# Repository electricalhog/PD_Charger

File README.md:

## Description
This prototype board is being used as a hardware test platform for the fully integrated project of the USB-C PD Charger. The PCB is designed to include all possible inputs/outputs and allow for troubleshooting, while interfacing with an off-the-shelf microcontroller board (NUCLEO-G431RB). Using discrete components that mirror the ideal setup will allow for full functionality and flexibilty in development.
## Testing
So far the board has been proven to work with ST's UCPDMon software as a Power Delivery Source and also control the 4-switch buck-boost controller.

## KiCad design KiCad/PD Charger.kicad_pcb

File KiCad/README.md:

# PD_Charger

*Schematic*

*Board rendering*

[Digi-Key Cart](https://www.digikey.com/en/mylists/list/EXQTTTFIJZ)

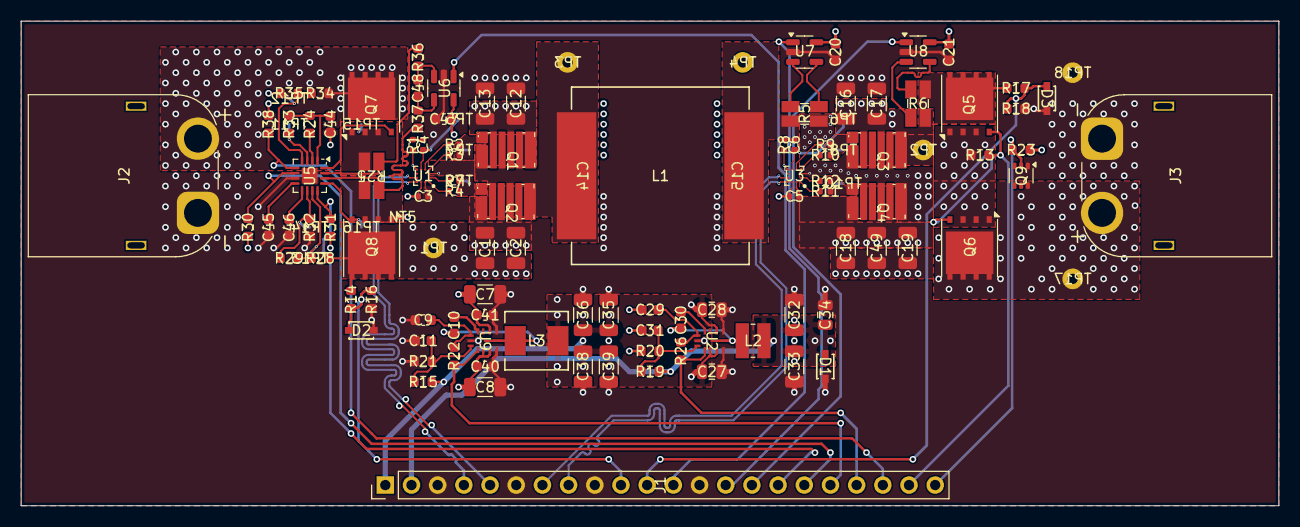
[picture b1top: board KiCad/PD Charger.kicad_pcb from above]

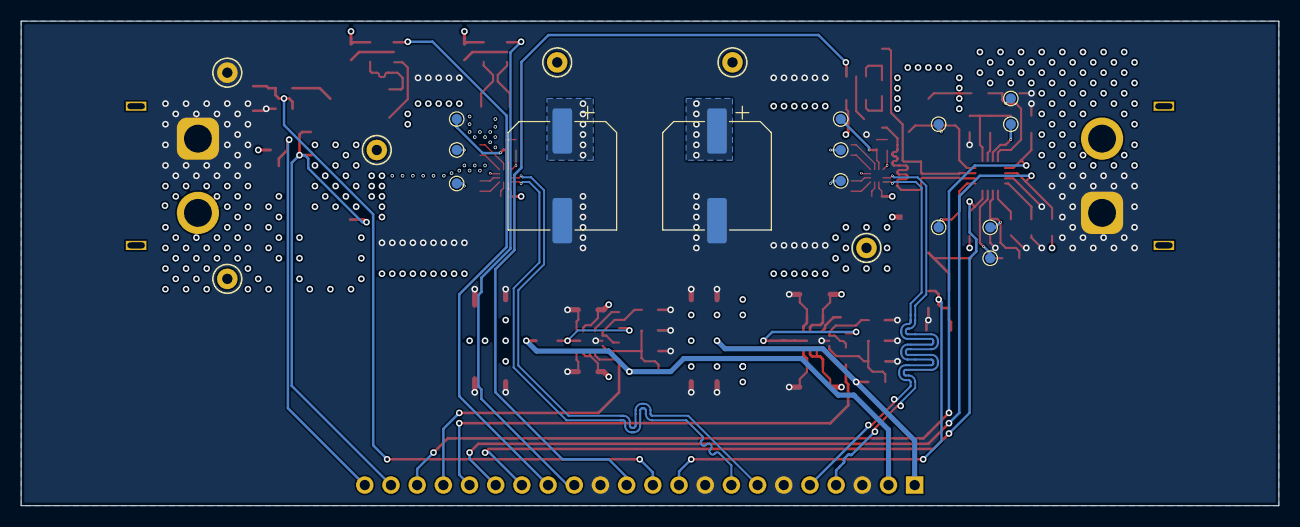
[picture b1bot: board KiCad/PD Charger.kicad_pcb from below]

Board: 4 copper layers, 122.0 x 47.0 mm, 123 parts (20 on the bottom side), 73 nets.

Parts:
C1, C2, C7, C8, C12, C13, C16, C17, C18, C19, C32, C33, C35, C36, C38, C39, C49: 10u; C_1206_3216Metric
C3, C5: 1u; C_0402_1005Metric
C4, C6: 100n; C_0402_1005Metric
C9, C29, C40, C41: 1u; C_0603_1608Metric
C10, C30: 100n; C_0603_1608Metric
C11, C31: 20p; C_0603_1608Metric
C14, C15: 82u; CP_Elec_10x7.9
C20, C21, C44, C47: 1uF; C_0603_1608Metric
C27, C28, C34: 0.47u; C_0805_2012Metric
C45: 20nF; C_0603_1608Metric
C46: 50nF; C_0603_1608Metric
C48: 1n; C_0603_1608Metric
D1, D2, D3: 3.425; CR_PLZ5V1C_VIS
J1: Conn_01x22; PinHeader_1x22_P2.54mm_Vertical
J2, J3: XT60_M; AMASS_XT60PW-M_1x02_P7.20mm_Horizontal
L1: 4.7u; L_Vishay_IHLP-6767
L2: 33u; L_Wuerth_MAPI-3015
L3: 10u; IND_PCC-M0530M-LP_PAN
NT5: NetTie_2; NetTie-2_SMD_Pad0.5mm
Q1, Q2, Q3, Q4: EPC2302; D0606F_100V
Q5, Q6, Q7, Q8: SiR5607DP; AO_DFN-8-1EP_5.55x5.2mm_P1.27mm_EP4.12x4.6mm
Q9: Q_Dual_NMOS_S1G1D2S2G2D1; SOT-363_SC-70-6
R1, R8: 0; R_0402_1005Metric
R2, R4, R9, R11: 2.2; R_0402_1005Metric
R3, R7, R10, R12: 1; R_0402_1005Metric
R5: 5m; R_Shunt_Ohmite_LVK12
R6: 12m; R_Shunt_Ohmite_LVK12
R13: 51k; R_0603_1608Metric
R14, R15, R17, R19, R22, R23, R26, R28, R30, R31, R38: 100k; R_0603_1608Metric
R16, R18: 5820; R_0603_1608Metric
R20: 43.2k; R_0603_1608Metric
R21: 24.9k; R_0603_1608Metric
R24, R33: 0; R_0603_1608Metric
R25: 2m; R_Shunt_Ohmite_LVK12
R29: 4.3k; R_0603_1608Metric
R32: 29k; R_0603_1608Metric
R34: 68k; R_0603_1608Metric
R35: 1.2k; R_0603_1608Metric
R36, R37: 10; R_0603_1608Metric
TP1, TP2, TP3, TP4, TP17, TP18: TestPoint; TestPoint_Keystone_5000-5004_Miniature
TP5, TP6, TP7, TP8, TP9, TP10, TP11, TP12, TP13, TP14, TP15, TP16: TestPoint; TestPoint_Pad_D1.0mm
U1, U3: WLCSP1.6x1.6-12B
U2: LMR36006BRNXT; RNX0012B
U5: ADM1270ACPZ; LFCSP-16-1EP_3x3mm_P0.5mm_EP1.5x1.5mm
U6: INA293A2; SOT-23-5
U7, U8: INA281A2; SOT-23-5
U9: LMR36015BRNXT; RNX0012B

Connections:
+3V3: C20.1, C21.1, C32.1, C33.1, C34.2, C47.1, D1.1 (K), J1.2, L2.2, R19.1, R23.2, R30.2, R31.2, U6.5 (V+), U7.5 (V+), U8.5 (V+)
+5V: C3.1, C5.1, C27.2, C28.2, C35.1, C36.1, C38.1, C39.1, J1.1, L3.2, R15.1, U1.A3 (VCC), U2.2 (VIN), U2.9 (EN), U2.10 (VIN), U3.A3 (VCC)
/3V3_GOOD: J1.19, R26.1, U2.8 (PG)
/3v3 Regulator/BST: C30.1, U2.4 (BST)
/3v3 Regulator/FB: C31.1, R19.2, R20.1, U2.7 (FB)
/3v3 Regulator/VCC: C29.1, R26.2, U2.5 (VCC)
/5V_GOOD: J1.18, R22.1, U9.8 (PG)
/5v Regulator/BST: C10.1, U9.4 (BST)
/5v Regulator/FB: C11.1, R15.2, R21.1, U9.7 (FB)
/5v Regulator/VCC: C9.1, R22.2, U9.5 (VCC)
/DC-DC/G1: Q1.1 (G), R2.2, R3.2, TP7.1
/DC-DC/G2: Q2.1 (G), R4.2, R7.2, TP9.1
/DC-DC/G3: Q3.1 (G), R9.2, R10.2, TP8.1
/DC-DC/G4: Q4.1 (G), R11.2, R12.2, TP10.1
/DC-DC/IDN: R6.3, U8.4 (Vin-)
/DC-DC/IDP: R6.2, U8.3 (Vin+)
/DC-DC/LSN: R5.3, U7.4 (Vin-)
/DC-DC/LSP: R5.2, U7.3 (Vin+)
/DC-DC/SW1: L1.1, Q1.2 (S), Q1.4 (S), Q1.6 (S), Q2.3 (D), Q2.5 (D), Q2.7 (D), R1.2, TP3.1, U1.C1 (PHASE), U1.D4 (PHASE)
/DC-DC/SW2: Q3.2 (S), Q3.4 (S), Q3.6 (S), Q4.3 (D), Q4.5 (D), Q4.7 (D), R5.4, R8.2, U3.C1 (PHASE), U3.D4 (PHASE)
/DC-DC/SW2a: L1.2, R5.1
/DC-DC/VOUTa: C15.1, C16.1, C17.1, C18.1, C19.1, C49.1, Q3.3 (D), Q3.5 (D), Q3.7 (D), R6.1, TP2.1
/ID_MON: J1.15, U8.1 (OUT)
/IL_MON: J1.14, U7.1 (OUT)
/INPUT_EN: J1.20, R38.2, U5.5 (ENABLE)
/IS_GOOD: J1.17, R30.1, U5.6 (~FAULT)
/IS_MON: J1.12, U6.1 (OUT)
/Input Protection/FB_PG: R29.1, R32.2, TP14.1, U5.10 (FB_PG)
/Input Protection/FLB: R28.1, R29.2, TP13.1, U5.11 (FLB)
/Input Protection/G_BP: Q8.4 (G), TP16.1, U5.13 (GATE)
/Input Protection/G_RP: Q7.4 (G), TP15.1, U5.16 (RPFG)
/Input Protection/ISET: R24.2, U5.2 (ISET)
/Input Protection/OV: R34.1, R35.2, TP12.1, U5.4 (OV)
/Input Protection/Q7_S: Q7.1 (S), Q7.2 (S), Q7.3 (S), R25.1
/Input Protection/Q8_S: NT5.2, Q8.1 (S), Q8.2 (S), Q8.3 (S), R25.4
/Input Protection/SENSE+: R25.2, R36.2, U5.15 (VCC)
/Input Protection/SENSE-: R25.3, R37.2, U5.14 (SENSE-)
/Input Protection/SENSE_FILTERED+: C48.2, R36.1, U6.3 (Vin+)
/Input Protection/SENSE_FILTERED-: C48.1, R37.1, U6.4 (Vin-)
/Input Protection/TIMER: C45.1, U5.8 (TIMER)
/Input Protection/TIMER_OFF: C46.1, U5.9 (TIMER_OFF)
/Input Protection/UV: R33.1, TP11.1, U5.3 (UV)
/Input Protection/VCAP: C44.1, R24.1, R33.2, U5.1 (VCAP)
/OUTPUT_DIS: J1.22, Q9.2 (G), R23.1
/OUTPUT_EN: J1.21, Q5.4 (G), Q6.4 (G), R13.2
/Output Switch/COM_S: Q5.1 (S), Q5.2 (S), Q5.3 (S), Q6.1 (S), Q6.2 (S), Q6.3 (S), R13.1
/PHASE_1_N: J1.5, U1.A4 (LI)
/PHASE_1_P: J1.4, U1.B4 (HI)
/PHASE_2_N: J1.8, U3.A4 (LI)
/PHASE_2_P: J1.7, U3.B4 (HI)
/VD_MON: D3.1 (K), J1.11, R17.2, R18.1
/VS_GOOD: J1.16, R31.1, U5.12 (PWRGD)
/VS_MON: D2.1 (K), J1.10, R14.2, R16.1
GND: C1.2, C2.2, C3.2, C5.2, C7.2, C8.2, C9.2, C11.2, C12.2, C13.2, C14.2, C15.2, C16.2, C17.2, C18.2, C19.2, C20.2, C21.2, C27.1, C28.1, C29.2, C31.2, C32.2, C33.2, C34.1, C35.2, C36.2, C38.2, C39.2, C40.2, C41.2, C44.2, C45.2, C46.2, C47.2, C49.2, D1.2 (A), D2.2 (A), D3.2 (A), J1.3, J1.6, J1.9, J1.13, J2.1, J3.1, Q2.2 (S), Q2.4 (S), Q2.6 (S), Q4.2 (S), Q4.4 (S), Q4.6 (S), Q9.1 (S), R16.2, R18.2, R20.2, R21.2, R32.1, R35.1, R38.1, TP18.1, U1.A2 (GND), U2.1 (PGND), U2.6 (AGND), U2.11 (PGND), U3.A2 (GND), U5.7 (GND), U5.17 (EP), U6.2 (GND), U7.2 (GND), U8.2 (GND), U9.1 (PGND), U9.6 (AGND), U9.11 (PGND)
unnamed: C4.2, R1.1
unnamed: C6.2, R8.1
unnamed: C4.1, TP5.1, U1.D3 (BOOT)
unnamed: R7.1, U1.B1 (LGH)
unnamed: R4.1, U1.A1 (LGL)
unnamed: R2.1, U1.D2 (UGH)
unnamed: R3.1, U1.D1 (UGL)
unnamed: C30.2, L2.1, U2.12 (SW)
unnamed: C6.1, TP6.1, U3.D3 (BOOT)
unnamed: R12.1, U3.B1 (LGH)
unnamed: R11.1, U3.A1 (LGL)
unnamed: R9.1, U3.D2 (UGH)
unnamed: R10.1, U3.D1 (UGL)
unnamed: C10.2, L3.1, U9.12 (SW)
VBUS: J3.2, Q6.5 (D), Q9.6 (D), TP17.1
VCC: C7.1, C8.1, C40.1, C41.1, NT5.1, U9.2 (VIN), U9.9 (EN), U9.10 (VIN)
VD: Q5.5 (D), R6.4, R17.1
VIN: J2.2, Q7.5 (D), R34.2
VS: C1.1, C2.1, C12.1, C13.1, C14.1, Q1.3 (D), Q1.5 (D), Q1.7 (D), Q8.5 (D), R14.1, R28.2, TP1.1

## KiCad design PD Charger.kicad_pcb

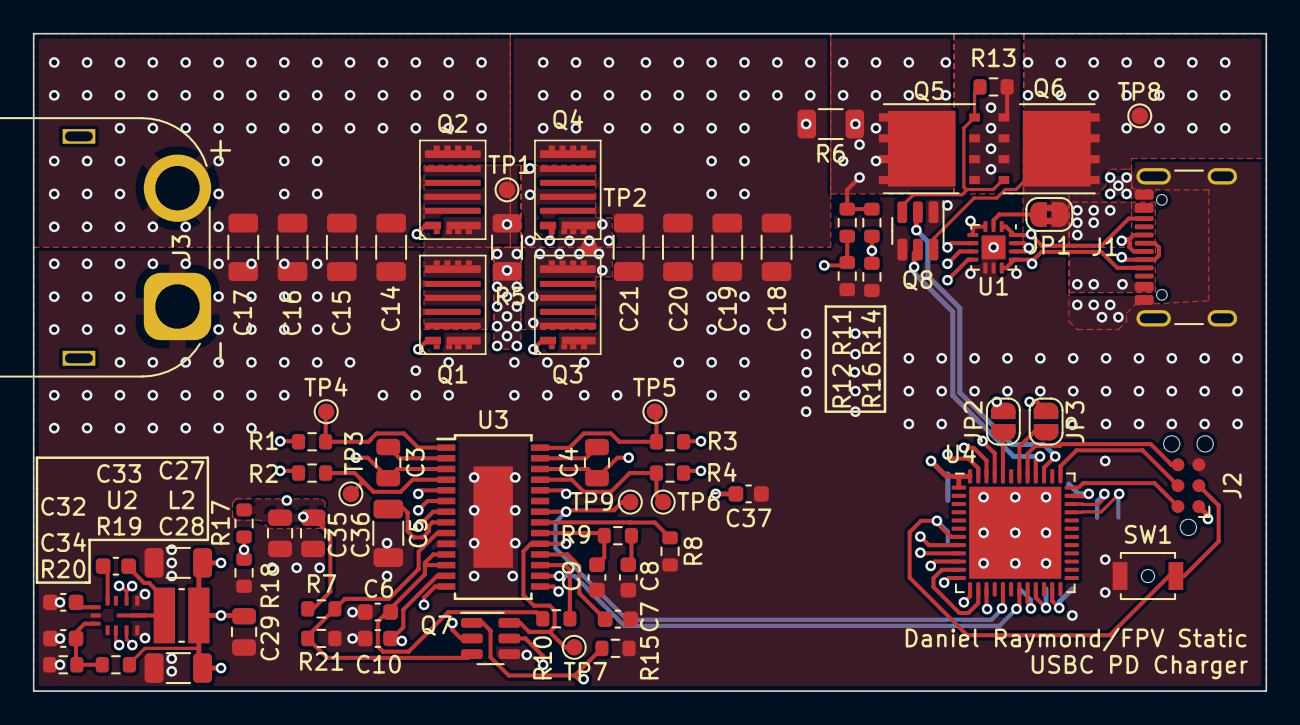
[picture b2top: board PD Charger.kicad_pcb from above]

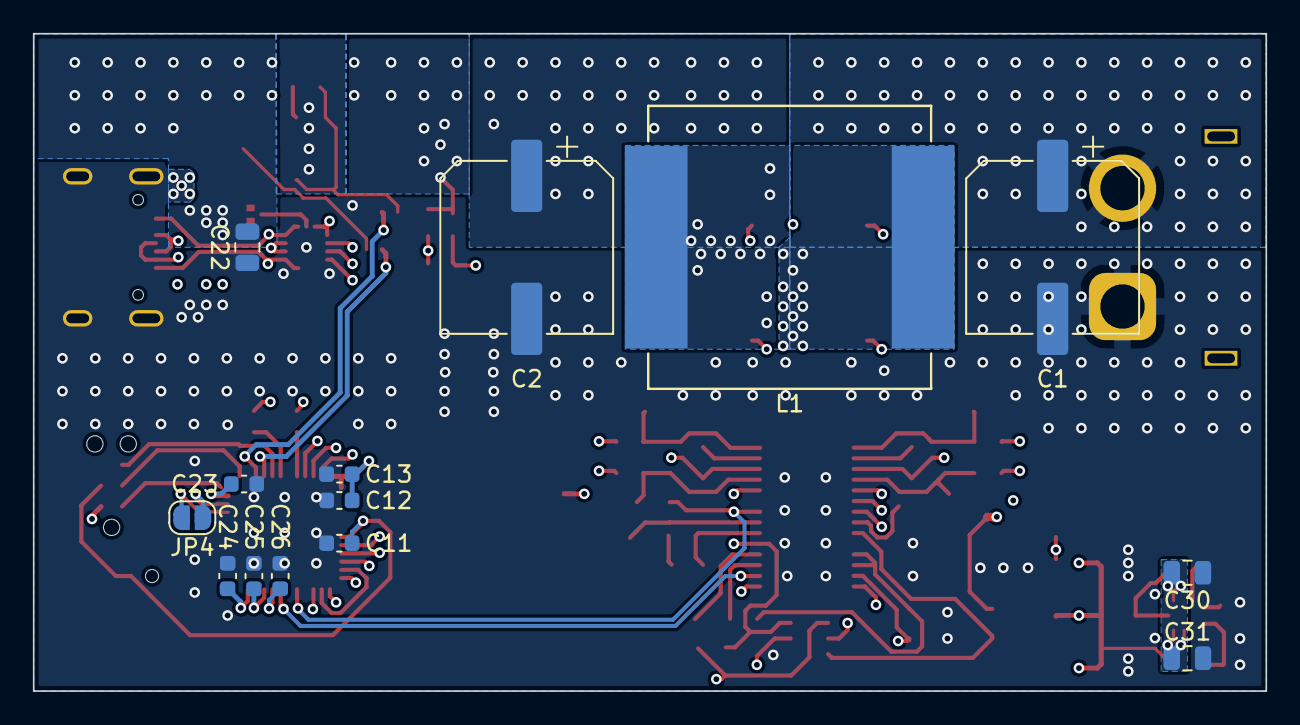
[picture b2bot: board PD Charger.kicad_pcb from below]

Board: 4 copper layers, 75.0 x 40.0 mm, 89 parts (14 on the bottom side), 60 nets.

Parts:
C1, C2: 82u; CP_Elec_10x7.9
C3, C4, C22, C29, C30, C31, C35, C36: 0.47u; C_0805_2012Metric
C5, C14, C15, C16, C17, C18, C19, C20, C21, C27, C28: 10u; C_1206_3216Metric
C6, C25: 0.47u; C_0603_1608Metric
C7, C12, C13, C23, C24: 0.1u; C_0603_1608Metric
C8: 4.7n; C_0603_1608Metric
C9: 100p; C_0603_1608Metric
C10: 4.7u; C_0603_1608Metric
C11, C26, C33: 100n; C_0603_1608Metric
C32, C37: 1u; C_0603_1608Metric
C34: 20p; C_0603_1608Metric
J1: USB_C_Receptacle_USB2.0; USB_C_Receptacle_GCT_USB4105-xx-A_16P_TopMnt_Horizontal
J2: Conn_ARM_SWD_TagConnect_TC2030; Tag-Connect_TC2030-IDC-NL_2x03_P1.27mm_Vertical
J3: XT60_M; AMASS_XT60PW-M_1x02_P7.20mm_Horizontal
JP1: SolderJumper_2_Bridged; SolderJumper-2_P1.3mm_Bridged2Bar_RoundedPad1.0x1.5mm
JP2, JP3, JP4: SolderJumper_2_Open; SolderJumper-2_P1.3mm_Open_RoundedPad1.0x1.5mm
L1: 4.7u; L_Vishay_IHLP-6767
L2: 33u; L_Wuerth_MAPI-3015
Q1, Q2, Q3, Q4: NMOS; ECP2302
Q5, Q6: NTMFS002P03; AO_DFN-8-1EP_5.55x5.2mm_P1.27mm_EP4.12x4.6mm
Q7, Q8: Q_Dual_NMOS_S1G1D2S2G2D1; SOT-23-6
R1, R2, R3, R4: 1; R_0603_1608Metric
R5: 5m; R_1206_3216Metric
R6: 20m; R_1206_3216Metric
R7, R10, R14, R17, R19: 100k; R_0603_1608Metric
R8, R13: 51k; R_0603_1608Metric
R9: 27k; R_0603_1608Metric
R11: 36k; R_0603_1608Metric
R12: 9k; R_0603_1608Metric
R15: 752; R_0603_1608Metric
R16, R18: 5820; R_0603_1608Metric
R20: 43.2k; R_0603_1608Metric
R21: 33k; R_0603_1608Metric
SW1: SW_MEC_5G; SW_SPST_B3U-1000P-B
TP1, TP2, TP3, TP4, TP5, TP6, TP7, TP8, TP9: TestPoint_Small; TestPoint_Pad_D1.0mm
U1: FUSB302B01MPX; WQFN-14-1EP_2.5x2.5mm_P0.5mm_EP1.45x1.45mm
U2: LMR36006BRNXT; RNX0012B
U3: LT8390xFE; TSSOP-28-1EP_4.4x9.7mm_P0.65mm
U4: STM32G431C6Ux; QFN-48-1EP_7x7mm_P0.5mm_EP5.6x5.6mm

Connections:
+3V3: C12.1, C13.1, C23.1, C24.1, C25.1, C27.1, C28.1, C29.2, J2.1 (VCC), L2.2, R19.1, U1.3 (VDD), U1.4 (VDD), U1.12 (VCONN), U1.13 (VCONN), U4.1 (VBAT), U4.21 (VDDA), U4.23 (VDD), U4.35 (VDD), U4.48 (VDD)
/CC1: J1.A5 (CC1), JP2.1 (A), U1.10 (CC1), U1.11 (CC1)
/CC2: J1.B5 (CC2), JP3.1 (A), U1.1 (CC2), U1.14 (CC2)
/COM_S: Q5.1 (S), Q5.2 (S), Q5.3 (S), Q6.1 (S), Q6.2 (S), Q6.3 (S), R13.1
/EN: Q7.3 (D), R7.2, R21.2, U3.9 (EN/UVLO)
/FB: Q7.6 (D), R11.1, R12.2, TP7.1, U3.19 (FB)
/G1: Q1.2 (G), R1.2
/G2: Q2.2 (G), R2.2
/G3: Q3.2 (G), R3.2
/G4: Q4.2 (G), R4.2
/INT_N: U1.5 (INT_N), U4.47 (PB9)
/ISMON: U3.16 (ISMON), U4.19 (PB2)
/LOADEN: Q8.5 (G), U4.40 (PC11)
/OUTDIS: Q8.2 (G), U4.39 (PC10)
/RT: R8.1, U3.21 (RT)
/SCL: U1.6 (SCL), U4.46 (PB8)
/SDA: U1.7 (SDA), U4.45 (PB7)
/SS: C7.1, U3.18 (SS)
/SWCLK: J2.4 (SWCLK), U4.37 (PA14)
/SWDIO: J2.2 (SWDIO), U4.36 (PA13)
/SWO: J2.6 (SWO), U4.41 (PB3)
/SYNC: TP9.1, U3.22 (SYNC/SPRD), U4.17 (PB0)
/USB_DN: J1.A7 (D-), J1.B7 (D-), JP4.2 (B), U4.33 (PA11)
/USB_DP: J1.A6 (D+), J1.B6 (D+), JP4.1 (A), U4.34 (PA12)
/VADJ: Q7.1 (S), R15.1, U4.15 (PA7)
/VADJ_AMP: U4.11 (PA3), U4.14 (PA6)
/VBUS: C22.2, J1.A4 (VBUS), J1.A9 (VBUS), J1.B4 (VBUS), J1.B9 (VBUS), JP1.2 (B), Q6.5 (D), Q8.6 (D), TP8.1
/VC: C9.1, R9.1, U3.20 (VC)
/VCTRLI: C10.1, U3.13 (CTRL1), U4.12 (PA4)
/VCTRLV: Q7.2 (G), U4.10 (PA2)
/VIN_SENSE: R17.2, R18.1, U4.8 (PA0)
/VOUT_SENSE: R14.2, R16.1, U4.9 (PA1)
/VREF: C6.1, R10.1, U3.11 (LOADEN), U3.12 (VREF)
/VREF+: C26.1, U4.20 (VREF+)
/~PGOOD: R10.2, U3.17 (~PGOOD)
/~RST: C11.1, J2.3 (~RESET), SW1.2, U4.7 (PG10)
/~RUN: Q7.5 (G), U4.13 (PA5)
GND: C1.2, C2.2, C5.2, C6.2, C7.2, C8.2, C9.2, C10.2, C11.2, C12.2, C13.2, C14.2, C15.2, C16.2, C17.2, C18.2, C19.2, C20.2, C21.2, C22.1, C23.2, C24.2, C25.2, C26.2, C27.2, C28.2, C29.1, C30.1, C31.1, C32.2, C34.2, C35.1, C36.1, C37.2, J1.A1 (GND), J1.A12 (GND), J1.B1 (GND), J1.B12 (GND), J1.S1 (SHIELD), J2.5 (GND), J3.1, Q1.3 (S), Q3.3 (S), Q7.4 (S), Q8.1 (S), Q8.4 (S), R8.2, R12.1, R15.2, R16.2, R18.2, R20.2, R21.1, SW1.1, U1.8 (GND), U1.9 (GND), U1.15 (GND), U2.1 (PGND), U2.6 (AGND), U2.11 (PGND), U3.10 (TEST), U3.29 (GND), U4.49 (VSS)
IS: C2.1, C18.1, C19.1, C20.1, C21.1, Q4.1 (D), R6.2, U3.14 (ISP)
LS: L1.1, R5.2, U3.6 (LSN)
unnamed: C8.1, R9.2
unnamed: JP1.1 (A), U1.2 (VBUS)
unnamed: JP2.2 (B), U4.44 (PB6)
unnamed: JP3.2 (B), U4.42 (PB4)
unnamed: Q5.4 (G), Q6.4 (G), Q8.3 (D), R13.2
unnamed: C33.1, U2.4 (BST)
unnamed: C34.1, R19.2, R20.1, U2.7 (FB)
unnamed: C33.2, L2.1, U2.12 (SW)
unnamed: C32.1, U2.5 (VCC)
unnamed: R1.1, TP4.1, U3.1 (BG1)
unnamed: R3.1, TP5.1, U3.28 (BG2)
unnamed: C3.1, U3.2 (BST1)
unnamed: C4.2, U3.27 (BST2)
unnamed: R2.1, TP3.1, U3.4 (TG1)
unnamed: R4.1, TP6.1, U3.25 (TG2)
SW1: C3.2, Q1.1 (D), Q2.3 (S), R5.1, TP1.1, U3.3 (SW1), U3.5 (LSP)
SW2: C4.1, L1.2, Q3.1 (D), Q4.3 (S), TP2.1, U3.26 (SW2)
VD: C37.1, Q5.5 (D), R6.1, R11.2, R14.1, U3.15 (ISN), U3.24 (VOUT)
VDD: C5.1, U3.8 (INTVCC)
VS: C1.1, C14.1, C15.1, C16.1, C17.1, C30.2, C31.2, C35.2, C36.2, J3.2, Q2.1 (D), R7.1, R17.1, U2.2 (VIN), U2.9 (EN), U2.10 (VIN), U3.7 (VIN)

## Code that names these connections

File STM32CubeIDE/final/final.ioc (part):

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Mcu.Name=STM32G474R(B-C-E)Tx
Mcu.Package=LQFP64
Mcu.UserName=STM32G474RETx
PA0.GPIOParameters=GPIO_Label
PA0.GPIO_Label=VS_MON
PA0.Mode=IN1-Single-Ended
PA0.Signal=ADC1_IN1
PA1.GPIOParameters=GPIO_Label
PA1.GPIO_Label=IL_MON
PA1.Signal=SharedAnalog_PA1
PA10.GPIOParameters=GPIO_Label
PA10.GPIO_Label=PHASE_2_P
PA10.Mode=Output_TB1TB2
PA10.Signal=HRTIM1_CHB1
PA11.GPIOParameters=GPIO_Label
PA11.GPIO_Label=PHASE_2_N
PA11.Mode=Output_TB1TB2
PA11.Signal=HRTIM1_CHB2
PA12.GPIOParameters=GPIO_PuPd,GPIO_Label
PA12.GPIO_Label=VS_GOOD
PA12.GPIO_PuPd=GPIO_PULLUP
PA12.Mode=Fault_Enable1
PA12.Signal=HRTIM1_FLT1
PA13.GPIOParameters=GPIO_Label
PA13.GPIO_Label=T_SWDIO
PA13.Mode=Serial_Wire
PA13.Signal=SYS_JTMS-SWDIO
PA14.GPIOParameters=GPIO_Label
PA14.GPIO_Label=T_SWCLK
PA14.Mode=Serial_Wire
PA14.Signal=SYS_JTCK-SWCLK
PA15.GPIOParameters=GPIO_PuPd,GPIO_Label
PA15.GPIO_Label=IS_GOOD
PA15.GPIO_PuPd=GPIO_PULLUP
PA15.Mode=Fault_Enable2
PA15.Signal=HRTIM1_FLT2
PA2.Mode=Asynchronous
PA2.Signal=LPUART1_TX
PA3.Mode=Asynchronous
PA3.Signal=LPUART1_RX
PA4.GPIOParameters=GPIO_Label
PA4.GPIO_Label=VS_MON
PA4.Mode=IN17-Single-Ended
PA4.Signal=ADC2_IN17
PA6.Mode=ExternalOutput
PA6.Signal=COMP1_OUT
PA8.GPIOParameters=GPIO_Label
PA8.GPIO_Label=PHASE_1_P
PA8.Mode=Output_TA1TA2
PA8.Signal=HRTIM1_CHA1
PA9.GPIOParameters=GPIO_Label
PA9.GPIO_Label=PHASE_1_N
PA9.Mode=Output_TA1TA2
PA9.Signal=HRTIM1_CHA2
PB0.GPIOParameters=GPIO_Label
PB0.GPIO_Label=IS_MON
PB0.Mode=IN15-Single-Ended
PB0.Signal=ADC1_IN15
PB3.GPIOParameters=GPIO_Label
PB3.GPIO_Label=T_SWO
PB3.Signal=SYS_JTDO-SWO
PB4.Mode=Source_AllSignals
PB4.Signal=UCPD1_CC2
PB6.Mode=Source_AllSignals
PB6.Signal=UCPD1_CC1
PB8-BOOT0.Mode=I2C
PB8-BOOT0.Signal=I2C1_SCL
PB9.Mode=I2C
PB9.Signal=I2C1_SDA
PC1.GPIOParameters=GPIO_Label
PC1.GPIO_Label=ID_MON
PC1.Mode=IN7-Single-Ended
PC1.Signal=ADC1_IN7
PC14-OSC32_IN.GPIOParameters=GPIO_Label
PC14-OSC32_IN.GPIO_Label=RCC_OSC32_IN
PC14-OSC32_IN.Mode=LSE-External-Oscillator
PC14-OSC32_IN.Signal=RCC_OSC32_IN
PC15-OSC32_OUT.GPIOParameters=GPIO_Label
PC15-OSC32_OUT.GPIO_Label=RCC_OSC32_OUT
PC15-OSC32_OUT.Mode=LSE-External-Oscillator
PC15-OSC32_OUT.Signal=RCC_OSC32_OUT
PC7.GPIOParameters=GPIO_Label
PC7.GPIO_Label=INPUT_EN
PC7.Signal=GPIO_Output
PC8.GPIOParameters=GPIO_Label
PC8.GPIO_Label=OUTPUT_EN
PC8.Signal=GPIO_Output
PC9.GPIOParameters=GPIO_Label
PC9.GPIO_Label=OUTPUT_DIS
PC9.Signal=GPIO_Output
PF0-OSC_IN.GPIOParameters=GPIO_Label
PF0-OSC_IN.GPIO_Label=RCC_OSC_IN
PF0-OSC_IN.Mode=HSE-External-Oscillator
PF0-OSC_IN.Signal=RCC_OSC_IN
PF1-OSC_OUT.GPIOParameters=GPIO_Label
PF1-OSC_OUT.GPIO_Label=RCC_OSC_OUT
PF1-OSC_OUT.Mode=HSE-External-Oscillator
PF1-OSC_OUT.Signal=RCC_OSC_OUT
RCC.HSE_VALUE=24000000
RCC.SYSCLKFreq_VALUE=170000000
RCC.SYSCLKSource=RCC_SYSCLKSOURCE_PLLCLK
board=NUCLEO-G474RE
boardIOC=true

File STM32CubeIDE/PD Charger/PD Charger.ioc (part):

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Mcu.Name=STM32G431C(6-8-B)Ux
Mcu.Package=UFQFPN48
Mcu.UserName=STM32G431C6Ux
PA0.Mode=INM
PA0.Signal=COMP1_INM
PA1.Mode=INP
PA1.Signal=COMP1_INP
PA10.GPIOParameters=GPIO_Label
PA10.GPIO_Label=INT_N
PA10.Signal=GPXTI10
PA13.Mode=Serial_Wire
PA13.Signal=SYS_JTMS-SWDIO
PA14.Mode=Serial_Wire
PA14.Signal=SYS_JTCK-SWCLK
PA2.Mode=Asynchronous
PA2.Signal=LPUART1_TX
PA3.Mode=Asynchronous
PA3.Signal=LPUART1_RX
PA4.GPIOParameters=GPIO_Label
PA4.GPIO_Label=VCTRL
PA4.Signal=COMP_DAC11_group
PA5.GPIOParameters=GPIO_Label
PA5.GPIO_Label=ICTRL
PA5.Signal=COMP_DAC12_group
PA6.GPIOParameters=GPIO_Label
PA6.GPIO_Label=VDMON
PA6.Mode=IN3-Single-Ended
PA6.Signal=ADC2_IN3
PA7.GPIOParameters=GPIO_Label
PA7.GPIO_Label=IDMON
PA7.Mode=IN4-Single-Ended
PA7.Signal=ADC2_IN4
PA8.Mode=I2C
PA8.Signal=I2C2_SDA
PA9.Mode=I2C
PA9.Signal=I2C2_SCL
PB0.Mode=Standalone
PB0.Signal=OPAMP3_VINP
PB1.Mode=Standalone
PB1.Signal=OPAMP3_VOUT
PB11.GPIOParameters=GPIO_Label
PB11.GPIO_Label=ISMON
PB11.Mode=IN14-Single-Ended
PB11.Signal=ADC1_IN14
PB12.GPIOParameters=GPIO_Label
PB12.GPIO_Label=REG_ON
PB12.Signal=GPIO_Input
PB13.GPIOParameters=GPIO_Label
PB13.GPIO_Label=PGOOD_N
PB13.Signal=GPIO_Input
PB14.GPIOParameters=GPIO_Label
PB14.GPIO_Label=SGOOD
PB14.Signal=GPIO_Input
PB15.GPIOParameters=GPIO_Label
PB15.GPIO_Label=FAULT_N
PB15.Signal=GPIO_Input
PB2.Mode=Standalone
PB2.Signal=OPAMP3_VINM
PB4.Mode=Source_AllSignals
PB4.Signal=UCPD1_CC2
PB6.Mode=Source_AllSignals
PB6.Signal=UCPD1_CC1
PB9.GPIOParameters=GPIO_Label
PB9.GPIO_Label=SYNC
PB9.Signal=S_TIM17_CH1
PC13.GPIOParameters=GPIO_Label
PC13.GPIO_Label=LOAD_DISCHRG
PC13.Signal=GPIO_Output
PC14-OSC32_IN.GPIOParameters=GPIO_Label
PC14-OSC32_IN.GPIO_Label=LOAD_EN
PC14-OSC32_IN.Signal=GPIO_Output
PC15-OSC32_OUT.GPIOParameters=GPIO_Label
PC15-OSC32_OUT.GPIO_Label=ENABLE
PC15-OSC32_OUT.Signal=GPIO_Output
PC4.GPIOParameters=GPIO_Label
PC4.GPIO_Label=VSMON
PC4.Mode=IN5-Single-Ended
PC4.Signal=ADC2_IN5
RCC.HSE_VALUE=8000000
RCC.SYSCLKFreq_VALUE=16000000
board=custom

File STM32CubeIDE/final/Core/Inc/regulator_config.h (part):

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
/**
 * VD_MON — Output voltage sense (V_out)
 * MCU pin : PA0 / ADC1_IN1
 * Net     : VD_MON (output.kicad_sch)
 * Physical: 100 kΩ / 5.82 kΩ resistive divider from V_out rail
 * Dir     : Analog input
 * NOTE    : IOC labels PA0 as VS_MON — this is an IOC labeling error.
 *           The schematic (higher priority) confirms PA0 = VD_MON (§2.2).
 */
#define PIN_VD_MON_PORT GPIOA
#define PIN_VD_MON_PIN GPIO_PIN_0
#define ADC_CHANNEL_VD_MON ADC_CHANNEL_1

/**
 * IL_MON — Inductor current sense
 * MCU pin : PA1 / ADC1_IN2 (shared with COMP1_INP)
 * Net     : IL_MON (dc-dc.kicad_sch)
 * Physical: INA281A2 (U7) output; 5 mΩ shunt (R5), 50 V/V gain
 * Dir     : Analog input (also COMP1 non-inverting input)
 */
#define PIN_IL_MON_PORT GPIOA
#define PIN_IL_MON_PIN GPIO_PIN_1
#define ADC_CHANNEL_IL_MON ADC_CHANNEL_2

/**
 * VS_MON_A4 — Input voltage sense (V_in)
 * MCU pin : PA4 / ADC2_IN17
 * Net     : VS_MON (input.kicad_sch)
 * Physical: 100 kΩ / 5.82 kΩ resistive divider from V_in rail
 * Dir     : Analog input
 * NOTE    : V_in is on ADC2 because PA4 is not available on ADC1 for
 *           this package (§8.5).
 */
#define PIN_VS_MON_PORT GPIOA
#define PIN_VS_MON_PIN GPIO_PIN_4
#define ADC_CHANNEL_VS_MON ADC_CHANNEL_17

/**
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 * Dir     : Analog input
 * Resolved: Round 3 Q2, confirmed from final.ioc pin labels (§3.3).
 */
#define PIN_ID_MON_PORT GPIOC
#define PIN_ID_MON_PIN GPIO_PIN_1
#define ADC_CHANNEL_ID_MON ADC_CHANNEL_7

/**
 * IS_MON — Input current sense (I_in, source current)
 * MCU pin : PB0 / ADC1_IN15
 * Net     : IS_MON (input.kicad_sch)
 * Physical: INA293A2 (U6) output; 5 mΩ shunt (R25, confirmed physical
 *           inspection), 50 V/V gain
 * Dir     : Analog input
 * Resolved: Round 3 Q2 + Q3 — R25 = 5 mΩ (schematic shows 2 mΩ, stale).
 */
#define PIN_IS_MON_PORT GPIOB
#define PIN_IS_MON_PIN GPIO_PIN_0
#define ADC_CHANNEL_IS_MON ADC_CHANNEL_15

/* =========================================================================
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
/**
 * COMP1_OUT — Comparator 1 output (routes to HRTIM EEV4)
 * MCU pin : PA6
 * Net     : COMP1_OUT (dc-dc.kicad_sch)
 * Physical: COMP1 output pin; connects HRTIM external event 4 (EEV4)
 * Dir     : Digital output (from COMP1 peripheral)
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
/**
 * PHASE_2_N (CHB2) — Timer B Output 2, output-side low-side FET drive
 * MCU pin : PA11 / HRTIM1_CHB2
 * Net     : PHASE_2_N (dc-dc.kicad_sch)
 * Physical: uP1966E (U3) low-side input; drives Q4 (EPC2306/EPC2302)
 * Dir     : Digital output (HRTIM-controlled, complementary to CHB1)
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
/**
 * VS_GOOD — Input power-good (HRTIM FLT1)
 * MCU pin : PA12 / HRTIM1_FLT1  (power board J1.16)
 * Net     : VS_GOOD = ADM1270 (U5) PWRGD, open-drain, R31 100k to +3V3
 * Physical: High when the switched input rail VS is above the FB_PG
 *           threshold: VS > 4.60 V rising / < 4.46 V falling
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 * Note    : Only meaningful while the input path is enabled, so the FLT
 *           interrupts are armed only in RUNNING (see regulator.c).
 */
#define PIN_VS_GOOD_PORT GPIOA
#define PIN_VS_GOOD_PIN GPIO_PIN_12

/**
 * IS_GOOD — Input over-current latch (HRTIM FLT2)
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 *           toggled low → high.
 * Dir     : Digital input, active-low (fault asserts when input goes LOW)
 */
#define PIN_IS_GOOD_PORT GPIOA
#define PIN_IS_GOOD_PIN GPIO_PIN_15

/* =========================================================================
 * SECTION 5: POWER PATH CONTROL GPIO
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 * Dir     : GPIO output
 * Usage   : Assert HIGH before enabling switching; deassert on fault/shutdown.
 */
#define PIN_INPUT_EN_PORT GPIOC
#define PIN_INPUT_EN_PIN GPIO_PIN_7

/**
 * ADM1270_COOLDOWN_MS — Minimum INPUT_EN low time after an ADM1270 current
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 * Dir     : GPIO output
 * Usage   : Assert HIGH before switching; deassert on fault/shutdown.
 */
#define PIN_OUTPUT_EN_PORT GPIOC
#define PIN_OUTPUT_EN_PIN GPIO_PIN_8

/**
 * OUTPUT_DIS — Discharges output path
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 * Dir     : GPIO output
 * Usage   : Assert (HIGH) during FAULT and IDLE states to bleed VBUS.
 */
#define PIN_OUTPUT_DIS_PORT GPIOC
#define PIN_OUTPUT_DIS_PIN GPIO_PIN_9

/* =========================================================================
 * SECTION 6: HRTIM TIMING CONSTANTS
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 *          to almost nothing.  The comparator path therefore works only for
 *          thresholds below roughly 150 mV (0.6 A); IL_MON has not been on a
 *          scope channel, so whether the INA281 output is slow, filtered or
 *          clipped before PA1 is open.
 */
#define DCM_MIN_ON_TIME_NS 100u

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 *                        limit, SW_OCP and the light-load exit: 1 ID_MON
 *                        (output shunt R6, after regulator_id_gain_permille
 *                        and _offset_ma), 0 IL_MON (after the IL gain,
 *                        offset and clipping correction; IL_MON is not
 *                        converted since 2026-10-22, so 0 reads 0 A).  Bench 2026-10-21,
 *                        forced CCM at 400 kHz into 25.3 ohm, 5-20 V: ID_MON
 *                        read 1.050 x V/R + 24 mA (the QT Py's idle draw is
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#define CCM_U0_BANDS             4u
#define CCM_U0_BAND_MV           { 7000u, 12000u, 17500u }   /* 5 / 9 / 15 / 20 V and the PPS between */
#if defined(BATTERY_LOAD) && (BATTERY_LOAD)
#define CCM_OCP_MA_DEFAULT       CCM_OCP_MA_FULL_SCALE   /* battery load: ID_MON's full scale (2026-11-12) */
#else
#define CCM_OCP_MA_DEFAULT       5000u   /* on regulator_ccm_i_avg_ma (ID_MON by default), capped at full scale */
#endif
#if defined(BATTERY_LOAD) && (BATTERY_LOAD)
#define CCM_ILIM_MA_DEFAULT      500u    /* battery load: what the pack takes until `bu battery` sets it */
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#define CCM_ILIM_KL_DEFAULT      400.0f  /* [V/(A s)], DCM */
#define CCM_ILIM_KL_CCM_DEFAULT  100.0f  /* [V/(A s)], CCM */
#define CCM_PEAK_MA_DEFAULT      0u      /* 0 = the PEAK_PROTECT backstop */
#define CCM_ILIM_SRC_DEFAULT     1u      /* ID_MON */
#define CCM_ENTRY_RAMP_DEFAULT   1u      /* CCM entry: the limit's reference from V_out (buck_ccm_limit_from) */
#define CCM_ILIM_FAST_DEFAULT    1u      /* the newest ADC2 scan (adc_monitor.h ADC_ID_LIMIT_SCANS) */
#define ID_GAIN_PERMILLE_DEFAULT 991
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#define CCM_OCP_CYCLES           20u     /* 1 ms */
/* SW_OCP at ID_MON's full scale (2026-11-12): with regulator_ccm_ilim_src 1 the level is never over
 * regulator_ccm_ocp_fs_ma = (ADC_ID_FULL_SCALE_MA - CCM_OCP_FS_SWING_MA) after regulator_id_gain_permille and
 * _offset_ma, so a current past what ID_MON can read still trips (its reading sits pinned over that level).  A level
 * at the last ADC count might not: the INA281 (U8) output swings to just under its supply, which is likely the 3.3 V
 * the ADC reads against (inference from the schematic's power symbols, not measured).  150 mA raw is 90 mV.
 * CCM_OCP_MA_FULL_SCALE in regulator_ccm_ocp_ma: the full-scale level alone. */
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#define POWER_FILTER_SHIFT 5u

/* =========================================================================
 * SECTION 7: SLOPE COMPENSATION TIMER (TIM6) CONSTANTS
 * =========================================================================*/

/**
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#define TIM6_PERIOD_COUNTS ((SYSCLK_HZ / TIM6_RATE_HZ) - 1u)

/* =========================================================================
 * SECTION 8: PID TIMER (TIM7) CONSTANTS
 * =========================================================================*/

/**
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 * at that rate (about 10 uA), a gain error that did not show at 12.5 kHz.
 * Recalibrate if the ADC1 sampling time, ratio or trigger rate changes. */
/* 2026-10-10: recalibrated against a meter after the X-NUCLEO-SRC1M1 came
 * off the G474, which changed the loading on PA0 and PA4 (Arduino A0, A2).
 * At a 15 V PD contract with no load, VBUS at TP2 read 13.32 V on the meter
 * while VD_MON averaged 15002 mV over 12 reads, and the supply read 24.56 V
 * while VS_MON averaged 20071 mV.  Both channels now sit near 1.16 x
 * nominal, VD_MON about 3 percent more (the sampling draw above).
 * Recalibrate whenever the wiring on PA0 or PA4 changes. */
/* 2026-10-12: D3 (the clamp on VD_MON) leaked ahead of its knee: the ADC
 * read 0.2, 0.9, 2.9 and 15.3 percent low at 20, 24, 28 and 36 V (meter at
 * TP2: 20.03, 24.22, 28.84, 42.5 V), so a 36 V contract put 42.5 V on VBUS.
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
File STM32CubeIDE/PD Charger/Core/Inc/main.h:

/* USER CODE BEGIN Header */
/**
  ******************************************************************************
  * @file           : main.h
  * @brief          : Header for main.c file.
  *                   This file contains the common defines of the application.
  ******************************************************************************
  * @attention
  *
  * Copyright (c) 2024 STMicroelectronics.
  * All rights reserved.
  *
  * This software is licensed under terms that can be found in the LICENSE file
  * in the root directory of this software component.
  * If no LICENSE file comes with this software, it is provided AS-IS.
  *
  ******************************************************************************
  */
/* USER CODE END Header */

/* Define to prevent recursive inclusion -------------------------------------*/
#ifndef __MAIN_H
#define __MAIN_H

#ifdef __cplusplus
extern "C" {
#endif

/* Includes ------------------------------------------------------------------*/
#include "stm32g4xx_hal.h"

/* Private includes ----------------------------------------------------------*/
/* USER CODE BEGIN Includes */
// #include "FUSB302.h"

/* USER CODE END Includes */

/* Exported types ------------------------------------------------------------*/
/* USER CODE BEGIN ET */

/* USER CODE END ET */

/* Exported constants --------------------------------------------------------*/
/* USER CODE BEGIN EC */

/* USER CODE END EC */

/* Exported macro ------------------------------------------------------------*/
/* USER CODE BEGIN EM */

/* USER CODE END EM */

void HAL_TIM_MspPostInit(TIM_HandleTypeDef *htim);

/* Exported functions prototypes ---------------------------------------------*/
void Error_Handler(void);

/* USER CODE BEGIN EFP */

/* USER CODE END EFP */

/* Private defines -----------------------------------------------------------*/
#define Vinsense_Pin GPIO_PIN_0
#define Vinsense_GPIO_Port GPIOA
#define Voutsense_Pin GPIO_PIN_1
#define Voutsense_GPIO_Port GPIOA
#define Vctrlv_Pin GPIO_PIN_2
#define Vctrlv_GPIO_Port GPIOA
#define Vadj_Pin GPIO_PIN_3
#define Vadj_GPIO_Port GPIOA
#define Vctrli_Pin GPIO_PIN_4
#define Vctrli_GPIO_Port GPIOA
#define VadjA6_Pin GPIO_PIN_6
#define VadjA6_GPIO_Port GPIOA
#define VadjA7_Pin GPIO_PIN_7
#define VadjA7_GPIO_Port GPIOA
#define nPGOOD_Pin GPIO_PIN_0
#define nPGOOD_GPIO_Port GPIOB
#define ISmon_Pin GPIO_PIN_1
#define ISmon_GPIO_Port GPIOB
#define ISmonB2_Pin GPIO_PIN_2
#define ISmonB2_GPIO_Port GPIOB
#define Discharge_Pin GPIO_PIN_10
#define Discharge_GPIO_Port GPIOC
#define Enable_Pin GPIO_PIN_11
#define Enable_GPIO_Port GPIOC
#define SYNC_Pin GPIO_PIN_3
#define SYNC_GPIO_Port GPIOB
#define I2C1_SDA_Pin GPIO_PIN_7
#define I2C1_SDA_GPIO_Port GPIOB
#define I2C1_SCL_Pin GPIO_PIN_8
#define I2C1_SCL_GPIO_Port GPIOB
#define I2C1_INT_Pin GPIO_PIN_9
#define I2C1_INT_GPIO_Port GPIOB

/* USER CODE BEGIN Private defines */

/* USER CODE END Private defines */

#ifdef __cplusplus
}
#endif

#endif /* __MAIN_H */

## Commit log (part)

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2024-04-13 v1.0
2024-04-13 file cleanup
2024-04-13 values updated
2024-04-15 DRC cleanup and added 3D models
2024-04-26 export for production
2024-04-29 silkscreen and testpoints
2024-04-29 Update image
2024-04-29 input fuse
2024-05-13 Updated file architecture
    KiCad and STM32CubeIDE project files combined to the same repository for lockstep version control
2024-05-13 updated photos
2024-05-16 peripherial control v0.1
2024-05-16 oops added twice
2024-05-16 oops wasn't added
2024-05-16 submodule updated
2024-05-16 variable type inconsistency
2024-05-16 board update from tested issues
2024-05-18 initial rust support - two rust bin targets, blink and i2c_scan (src/bin) - probe-rs vscode integration (launch.json) - requisite project / cargo setup
2024-05-19 board update
2024-05-19 separation of branches
2024-05-19 fusb library
2024-05-19 board images
2024-05-21 better usbc & fusb302 routing
2024-05-29 software slewing
2024-06-06 remove empty fusb.rs file
2024-07-22 multisheet design
2024-09-12 new layout
2024-11-08 multi sheet redesign
2024-12-06 standalone regulator core
2024-12-06 3d models updated
2024-12-12 finishing touches
2024-12-30 UCPD Source Test
2025-01-07 test pd source
2025-01-07 production files
2025-01-15 PWM output
2025-01-16 Complementary PWM output
2025-02-19 buck-boost operation
2025-02-20 preliminary testing
2025-02-20 media
2025-02-20 excel screenshop
2025-02-20 excel screenshot
2025-10-23 firmware outline
2025-10-29 stmcube changes
2025-10-29 documentation
2025-11-10 STMCubeIDE based project
2025-11-10 compile outside of IDE
2025-11-17 test pwm output
2025-11-20 stm32cube comparator setup
2026-02-21 closed loop control
2026-03-10 updated pinref and serial debug
2026-03-10 clean start
2026-03-10 nlspec
2026-03-10 Initial plan
2026-03-10 Implement power stage per NLSpec: regulator_config.h, power_stage.h, power_stage.c; fix state_machine.c; expand PDO table; wire USBPD callbacks
2026-03-10 Fix code review issues: remove duplicate comment, fix misleading TIM7 comment, clean HRTIM constant names
2026-03-11 fresh build
2026-03-11 NVIC priority change
2026-03-11 reference nl spec
2026-03-11 remove unnecessary projects
2026-03-11 NVIC priority fix
2026-03-11 nlspec spec
2026-03-11 ready for agent implementation
2026-03-11 feat: implement NLSpec regulator firmware (regulator, pid, slope_comp, adc_monitor, pd_interface modules)
2026-03-11 fix: address code review issues (slope arg, mode transition, inductor constant, HRTIM reconfigure)
2026-03-13 fixes for build
2026-03-13 Bootstrap reset design, TIM7 IRQ fix, default regulation test task
2026-03-13 debug
2026-03-14 switch to cmake
2026-03-14 timer blanking and backstop
2026-03-14 Reassign HRTIM CMP1=blanking/CMP2=backstop/CMP3=bootstrap; add debug_log ring buffer
2026-03-14 Fix FreeRTOS ISR priority violations: UCPD1 priority 4→5, TRACER_EMB LPUART1/DMA 3/0→5
2026-03-15 Fix stale v_in_mv=0 in regulator_start() causing wrong BOOST mode and immediate VIN_RANGE fault
2026-03-15 interrupt issues
2026-04-17 Address PR review: buck-boost future-proofing, SlopeCompMode cross-ref, debug TODOs
    Agent-Logs-Url: https://github.com/electricalhog/PD_Charger/sessions/e7d0bb3b-56a4-40c5-a1f2-676c5321d41a
2026-04-17 build changes
2026-04-17 Fix post-switching freeze; add four-switch buck-boost mode (v0.1.2k)
    Debug pass on the hardware freeze that hit immediately after the first
    switching waveforms came up on v0.1.2j. Two independent root causes
    were found; both are fixed, and the NL spec is bumped to v0.1.2k with
    the findings and the new operating mode written up.
    Freeze root cause #1 — HRTIM period placeholder never overwritten.
    MX_HRTIM1_Init() applies a shared HRTIM_TimeBaseCfgTypeDef with
